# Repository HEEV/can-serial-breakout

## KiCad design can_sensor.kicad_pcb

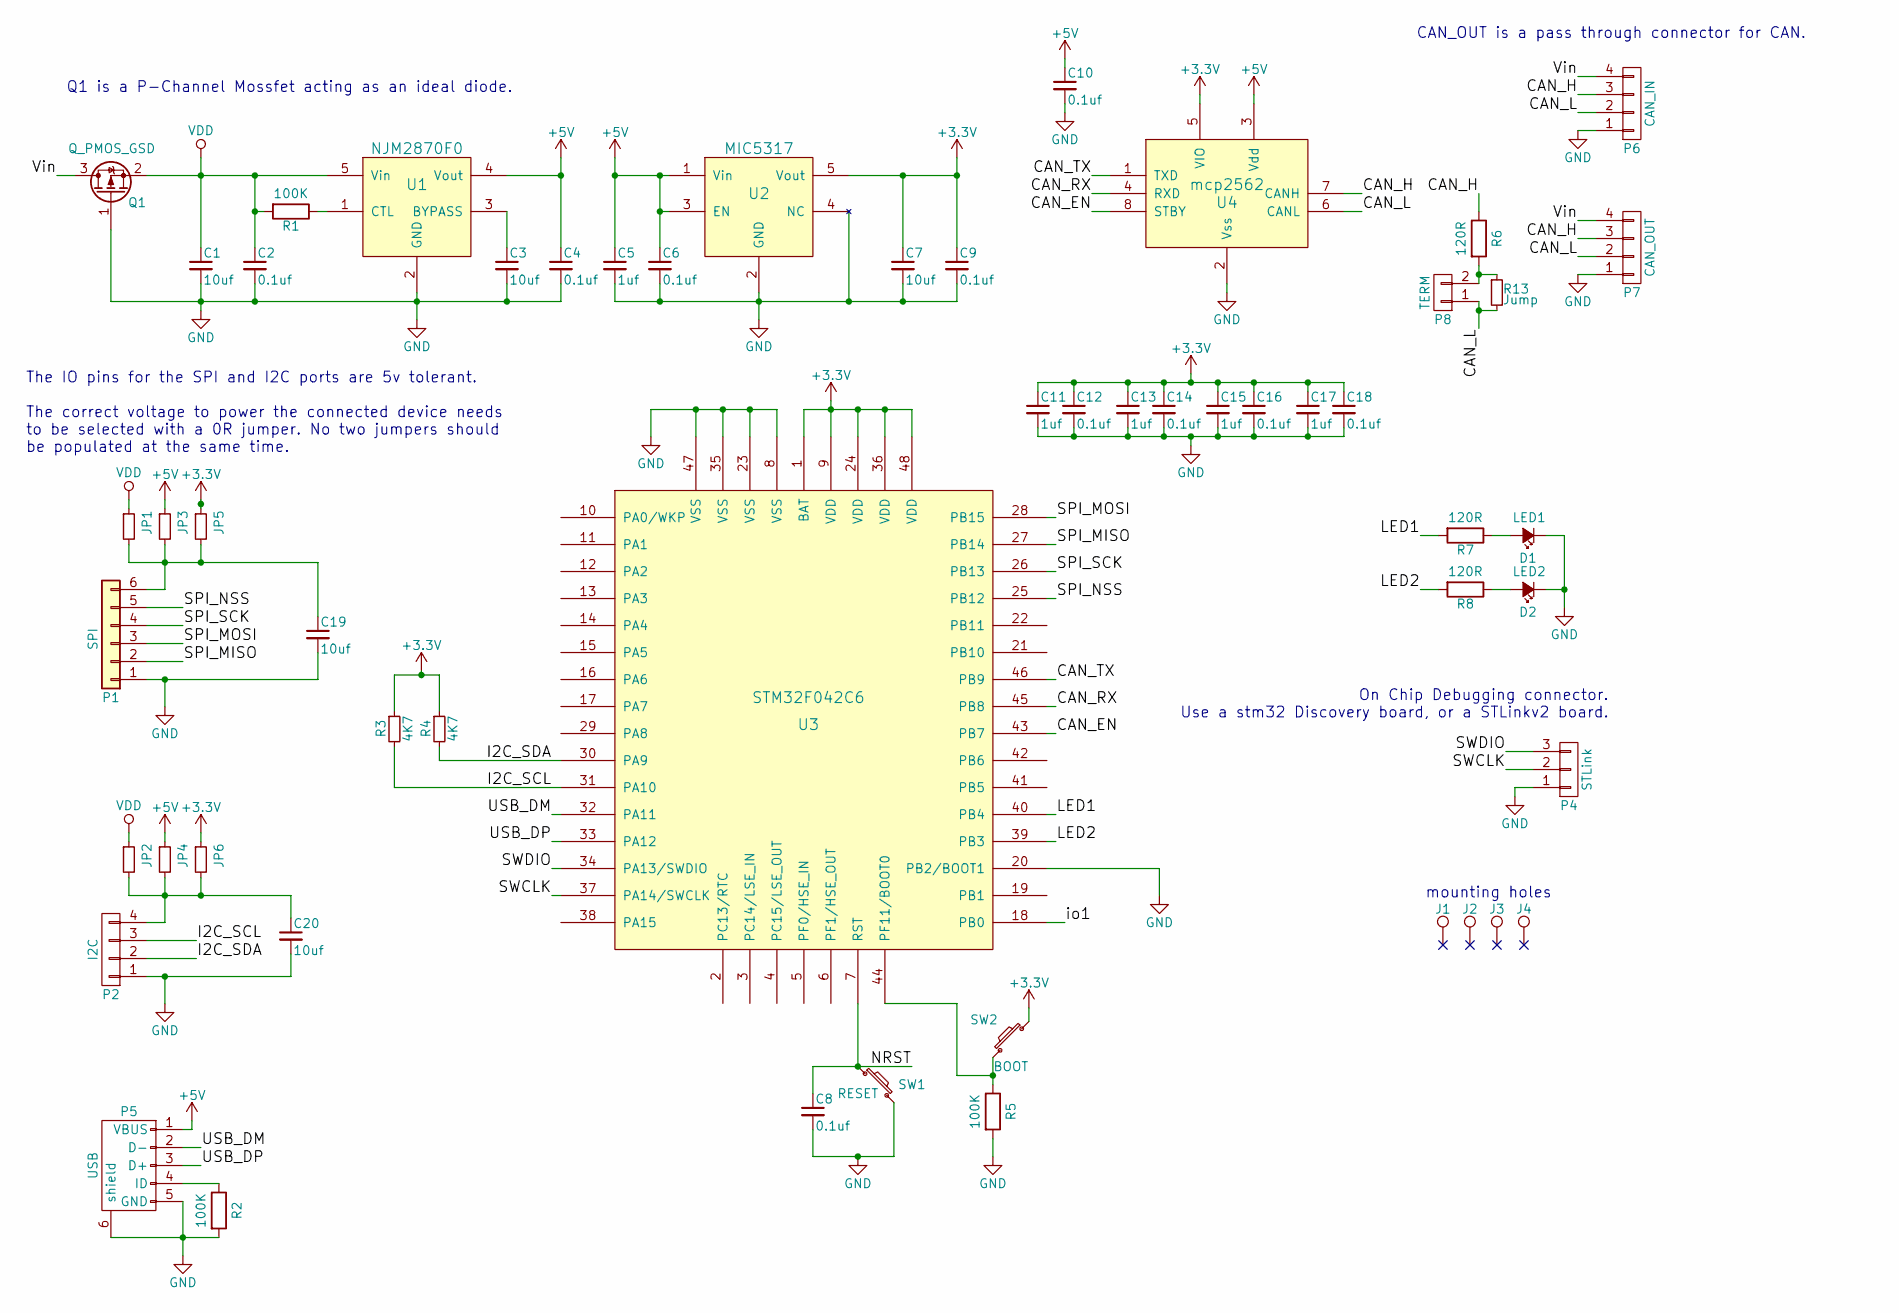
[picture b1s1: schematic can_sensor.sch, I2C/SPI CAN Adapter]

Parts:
C1, C3, C7, C19, C20: 10uf; C_0603_HandSoldering
C2, C4, C6, C8, C9, C10, C12, C14, C16, C18: 0.1uf; C_0603_HandSoldering
C5, C11, C13, C15, C17: 1uf; C_0603_HandSoldering
D1: LED1; LED_0603_HandSoldering
D2: LED2; LED_0603_HandSoldering
J1, J2, J3, J4: TEST_1P; MountingHole_3.2mm_M3_ISO7380_Pad
JP1, JP2: Vin; R_0603_HandSoldering
JP3, JP4: 3V; R_0603_HandSoldering
JP5, JP6: 5V; R_0603_HandSoldering
P1: SPI; Molex-duraClick-6conn
P2: I2C; Molex-duraClick-4conn
P4: STLink; Pin_Header_Straight_1x03
P5: USB; USB_Micro-B
P6: CAN_IN; Molex-duraClick-4conn
P7: CAN_OUT; Molex-duraClick-4conn
P8: TERM; Pin_Header_Straight_1x02_Pitch2.54mm
Q1: Q_PMOS_GSD; SOT-23_Handsoldering
R1, R2, R5: 100K; R_0603_HandSoldering
R3, R4: 4K7; R_0805
R6, R7, R8: 120R; R_0603_HandSoldering
R13: Jump; R_0603
SW1: RESET; SW_SPST_FSMSM
SW2: BOOT; SW_SPST_FSMSM
U1: NJM2870F0; SOT-23-5
U2: MIC5317; SOT-23-5
U3: STM32F042C6; TQFP-48_7x7mm_Pitch0.5mm
U4: mcp2562; SOIC-8-N

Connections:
+3V3: C7.1, C9.1, C11.1, C12.1, C13.1, C14.1, C15.1, C16.1, C17.1, C18.1, JP5.1, JP6.1, R3.1, R4.1, SW2.1, U2.5 (Vout), U3.1 (BAT), U3.9 (VDD), U3.24 (VDD), U3.36 (VDD), U3.48 (VDD), U4.5 (VIO)
+5V: C4.1, C5.1, C6.1, C10.1, JP3.1, JP4.1, P5.1 (VBUS), U1.4 (Vout), U2.1 (Vin), U2.3 (EN), U4.3 (Vdd)
/CAN_EN: U3.43 (PB7), U4.8 (STBY)
/CAN_H: P6.3, P7.3, R6.1, U4.7 (CANH)
/CAN_L: P6.2, P7.2, P8.1, R13.2, U4.6 (CANL)
/CAN_RX: U3.45 (PB8), U4.4 (RXD)
/CAN_TX: U3.46 (PB9), U4.1 (TXD)
/I2C_SCL: P2.3, R3.2, U3.31 (PA10)
/I2C_SDA: P2.2, R4.2, U3.30 (PA9)
/LED1: R7.2, U3.40 (PB4)
/LED2: R8.2, U3.39 (PB3)
/NRST: C8.1, SW1.1, U3.7 (RST)
/SPI_MISO: P1.2, U3.27 (PB14)
/SPI_MOSI: P1.3, U3.28 (PB15)
/SPI_NSS: P1.5, U3.25 (PB12)
/SPI_SCK: P1.4, U3.26 (PB13)
/SWCLK: P4.2, U3.37 (PA14/SWCLK)
/SWDIO: P4.3, U3.34 (PA13/SWDIO)
/USB_DM: P5.2 (D-), U3.32 (PA11)
/USB_DP: P5.3 (D+), U3.33 (PA12)
/Vin: P6.4, P7.4, Q1.3 (D)
/io1: U3.18 (PB0)
GND: C1.2, C2.2, C3.2, C4.2, C5.2, C6.2, C7.2, C8.2, C9.2, C10.2, C11.2, C12.2, C13.2, C14.2, C15.2, C16.2, C17.2, C18.2, C19.2, C20.2, D1.1 (K), D2.1 (K), P1.1, P2.1, P4.1, P5.5 (GND), P5.6 (shield), P6.1, P7.1, Q1.1 (G), R2.2, R5.2, SW1.2, U1.2 (GND), U2.2 (GND), U2.4 (NC), U3.8 (VSS), U3.20 (PB2/BOOT1), U3.23 (VSS), U3.35 (VSS), U3.47 (VSS), U4.2 (Vss)
unnamed: C3.1, U1.3 (BYPASS)
unnamed: C19.1, JP1.2, JP3.2, JP5.2, P1.6
unnamed: C20.1, JP2.2, JP4.2, JP6.2, P2.4
unnamed: D1.2 (A), R7.1
unnamed: D2.2 (A), R8.1
unnamed: P5.4 (ID), R2.1
unnamed: P8.2, R6.2, R13.1
unnamed: R1.1, U1.1 (CTL)
unnamed: R5.1, SW2.2, U3.44 (PF11/BOOT0)
VDD: C1.1, C2.1, JP1.1, JP2.1, Q1.2 (S), R1.2, U1.5 (Vin)

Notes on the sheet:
CAN_OUT is a pass through connector for CAN.
On Chip Debugging connector. Use a stm32 Discovery board, or a STLinkv2 board.
Q1 is a P-Channel Mossfet acting as an ideal diode.
mounting holes
The IO pins for the SPI and I2C ports are 5v tolerant. The correct voltage to power the connected device needs to be selected with a 0R jumper. No two jumpers should be populated at the same time.

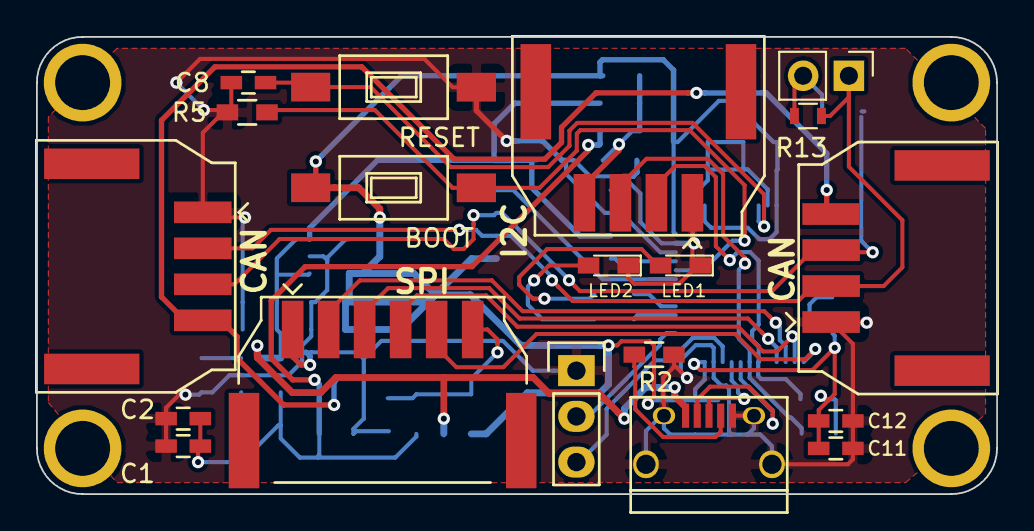
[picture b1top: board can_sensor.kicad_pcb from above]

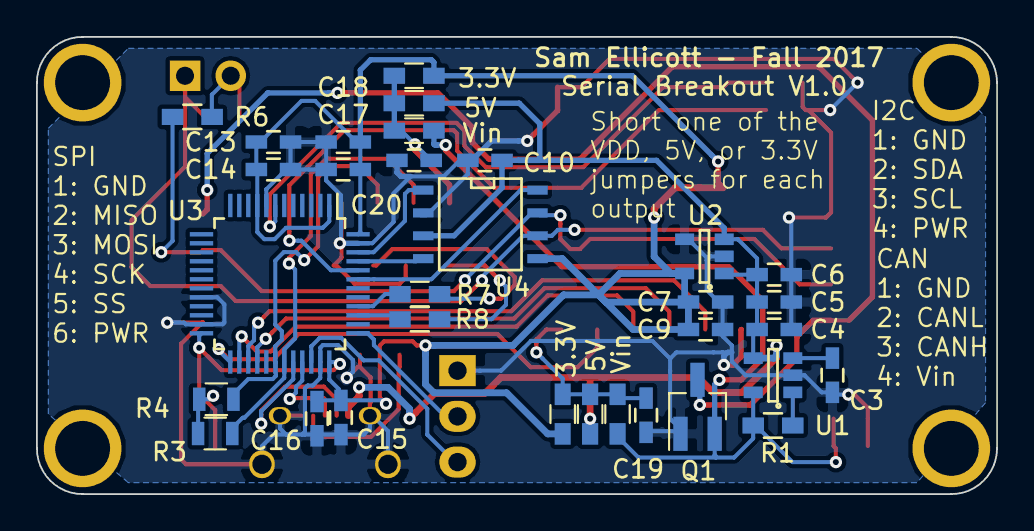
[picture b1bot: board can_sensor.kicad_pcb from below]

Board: 2 copper layers, 53.3 x 25.4 mm, 55 parts (32 on the bottom side), 32 nets.

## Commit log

2017-10-25 Initial commit based on the can-breakout PCB.
2017-10-25 Added SPI and I2C connectors to the schematic
2017-10-25 Added footprints to most components
2017-10-27 finished adding footprints & started routing
2017-12-04 Changed title and added pdf
